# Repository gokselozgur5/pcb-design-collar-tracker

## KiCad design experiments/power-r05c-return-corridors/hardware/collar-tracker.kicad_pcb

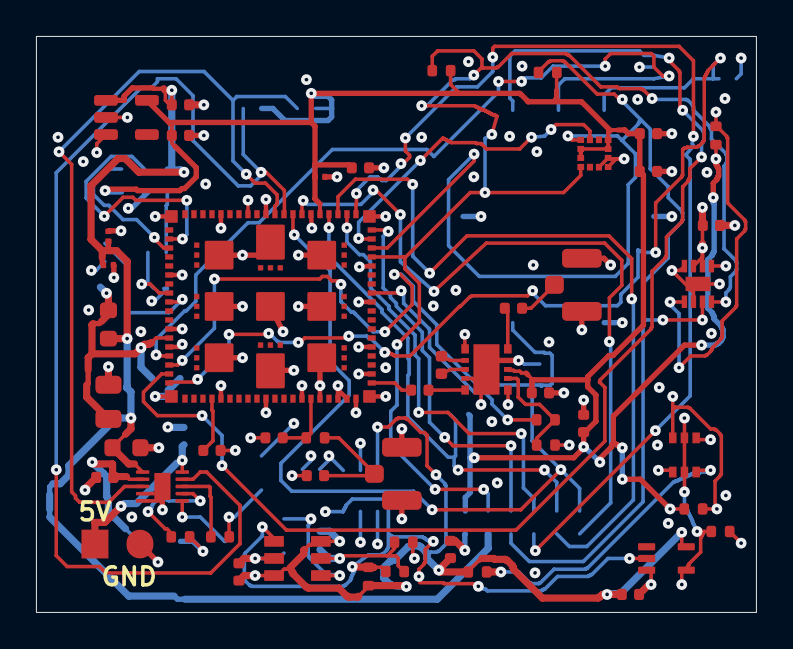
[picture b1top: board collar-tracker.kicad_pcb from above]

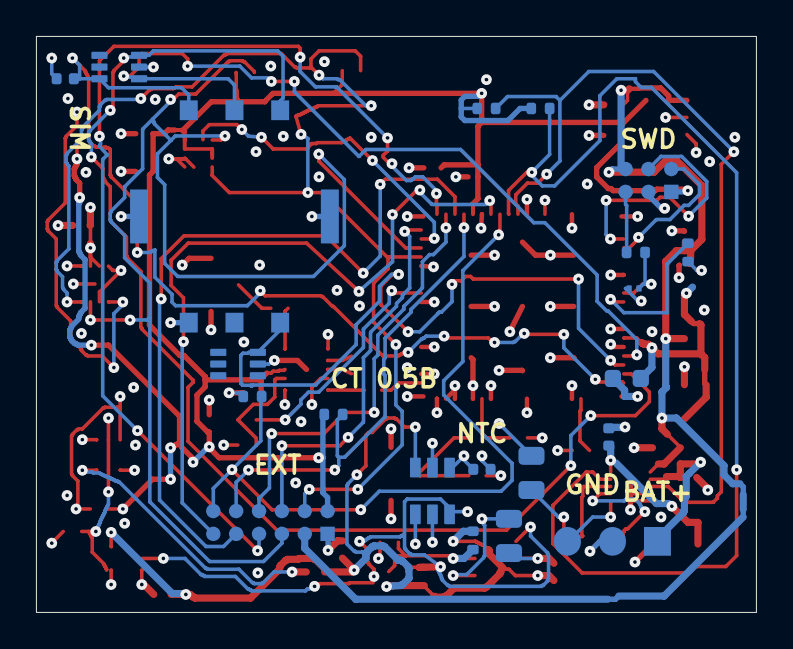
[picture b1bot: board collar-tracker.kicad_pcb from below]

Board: 4 copper layers, 40.0 x 32.0 mm, 71 parts (21 on the bottom side), 49 nets.

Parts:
C1: 1uF /10V; C1_C_0201_0603Metric
C2: 1uF /10V; C2_C_0201_0603Metric
C3: 47uF /10V; C3_C_0805_2012Metric
C4: 10uF /10V; C4_C_0603_1608Metric
C5: 100nF; C5_C_0201_0603Metric
C6: 4.7uF; C6_C_0402_1005Metric
C7: 4.7uF; C7_C_0402_1005Metric
C8: 100nF; C8_C_0201_0603Metric
C9: 1uF /16V X7R; C9_C_0805_2012Metric
C10: 100nF; C10_C_0402_1005Metric
C11: DNP / tune; C11_C_0402_1005Metric
C12: DNP / tune; C12_C_0402_1005Metric
C13: 39pF RF; C13_C_0402_1005Metric
C14: 39pF RF; C14_C_0402_1005Metric
C15: 100nF; C15_C_0402_1005Metric
C16: 1uF; C16_C_0402_1005Metric
C17: 1uF /10V; C17_C_0402_1005Metric
C18: 10uF /10V; C18_C_0603_1608Metric
C19: 1uF /10V; C19_C_0402_1005Metric
C20: 1uF; C20_C_0402_1005Metric
C21: 1uF; C21_C_0402_1005Metric
C23: 100nF; C23_C_0402_1005Metric
C24: 100nF; C24_C_0402_1005Metric
C25: 680nF /25V X7R; C25_C_0805_2012Metric
C26: 47nF /16V X7R; C26_C_0402_1005Metric
C27: 100nF /16V X7R; C27_C_0402_1005Metric
C28: 100nF /16V X7R; C28_C_0402_1005Metric
C29: 100nF /16V X7R; C29_C_0402_1005Metric
C30: 100nF /16V X7R; C30_C_0402_1005Metric
D1, D2: TPD4E1U06DCKR
FB1: 22R @100MHz; FB1_L_0603_1608Metric
J1: LTE antenna / 50R; J1_U.FL_Hirose_U.FL-R-SMT-1_Vertical
J2: GNSS antenna / passive; J2_U.FL_Hirose_U.FL-R-SMT-1_Vertical
J3: 5V charging input; J3_Solder_1x02_P2.5mm
J4: Protected cell + NTC; J4_Solder_1x03_P2.5mm
J5: DIGITAL health sensor interface; J5_Contact_2x06_P1.27mm
J6: SIM8051-6-0-14-00-A; SIM8051_6_0_14_00_A
J7: SWD / debug; J7_Contact_2x03_P1.27mm
L1: 9.1nH; L1_L_0402_1005Metric
Q1: DMN62D2UDW-7; Q1_SOT-363_SC-70-6
R1: 22k /1%; R1_R_0402_1005Metric
R2: 1k; R2_R_0402_1005Metric
R3: 0R / tune; R3_R_0402_1005Metric
R4: 1k; R4_R_0402_1005Metric
R5: 100k; R5_R_0402_1005Metric
R6: 18k /1%; R6_R_0402_1005Metric
R7: 3k /1%; R7_R_0402_1005Metric
R8: 10k; R8_R_0402_1005Metric
R9: 10k; R9_R_0402_1005Metric
R12: 4.7k; R12_R_0402_1005Metric
R13: 4.7k; R13_R_0402_1005Metric
R14: 100k; R14_R_0402_1005Metric
R15: 100k; R15_R_0402_1005Metric
R16: 10k /1%; R16_R_0402_1005Metric
R17: 1M /0.1%; R17_R_0402_1005Metric
R18: 130k /0.1%; R18_R_0402_1005Metric
R19: 16.9M /1%; R19_R_0402_1005Metric
R20: 10k /1%; R20_R_0402_1005Metric
R21: 22R /1%; R21_R_0402_1005Metric
R22: 1M /1%; R22_R_0402_1005Metric
R23: 100k /1%; R23_R_0402_1005Metric
U1: nRF9151-LACA; U1_LGA_9151_12.1x11.1mm
U2: SKY65943-11; U2_SKY65943_DK10171
U3: BQ25185DLHR; U3_Texas_DLH0010A_WSON-10-1EP_2.2x2mm_P0.4mm_EP0.9x1.5mm
U4: TPS7A0218PDBVR; U4_SOT-23-5
U5: LIS2DW12TR; U5_LGA-12_2x2mm_P0.5mm
U6: TPS3808G01DBVR; U6_SOT-23-6
U7: TPS3808G30DBVR; U7_SOT-23-6
U8: SN74LVC1G14DCKR; U8_SOT-353_SC-70-5
U9: MAX17048G+T10; U9_MAX17048_T822_3_90_0065E

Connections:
/ACC_INT: U1.58, U5.12
/AMP_IN: L1.2, U2.8
/BAT_NTC: J4.3, U3.6
/CHG_FAULT: R9.1, U1.70, U3.3
/CHG_STAT: R8.1, U1.69, U3.9
/COEX0: R4.1, U1.52
/DEBUG_RESET: J7.5, R2.2
/DEC0: C7.1, U1.24
/FG_ALERT: R23.2, U1.73, U9.5
/FILT_OUT: L1.1, U2.7
/GND: C1.2, C2.2, C3.2, C4.2, C5.2, C6.2, C7.2, C8.2, C9.2, C10.2, C11.2, C12.2, C15.2, C16.2, C17.2, C18.2, C19.2, C20.2, C21.2, C23.2, C24.2, C25.2, C26.2, C27.2, C28.2, C29.2, C30.2, D1.2, D2.2, J1.2, J2.2, J3.2, J4.2, J5.1, J6.5, J6.8, J7.3, Q1.1, Q1.4, R5.2, R6.2, R7.2, R15.2, R18.2, R22.2, U1.1, U1.7, U1.13, U1.15, U1.20, U1.25, U1.30, U1.34, U1.36, U1.38, U1.39, U1.40, U1.41, U1.43, U1.46, U1.51, U1.55, U1.60, U1.66, U1.71, U1.76, U1.105, U1.106, U1.107, U1.108, U1.109, U1.110, U1.111, U1.112, U1.113, U2.1, U2.4, U2.6, U2.9, U2.11, U3.4, U3.5, U3.11, U4.2, U5.6, U5.7, U5.8, U6.2, U7.2, U8.3, U9.1, U9.4, U9.6, U9.9
/GNSS_ANT: C14.1, J2.1
/GNSS_FEM_IN: C14.2, U2.5
/GNSS_FEM_OUT: C13.1, U2.10
/GNSS_LNA_EN: R4.2, R5.1, U2.2
/GPS_RF: C13.2, U1.42
/HEALTH_CS: J5.10, R14.1, U1.64
/HEALTH_EN: J5.12, R15.1, U1.68
/HEALTH_INT: J5.6, U1.59
/HEALTH_RESET: J5.11, U1.67
/I2C_SCL: J5.5, R13.1, U1.57, U5.1, U9.7
/I2C_SDA: J5.4, R12.1, U1.56, U5.4, U9.8
/ILIM_VSET: R6.1, U3.7
/ISET: R7.1, U3.8
/LTE_ANT: C12.1, J1.1, R3.2
/LTE_RF: C11.1, R3.1, U1.35
/NRF_ENABLE: C9.1, R1.2, U1.10, U7.5
/NRF_RESET: C8.1, R2.1, U1.9
/POWER_FAULT: Q1.2, Q1.5, R22.1, U8.4
/POWER_GOOD: R1.1, R16.2, R19.1, U6.1, U7.3, U8.2
/SIM_1V8: C10.1, D1.6, J6.1, U1.19
/SIM_CLK: D1.3, J6.3, U1.18
/SIM_IO: D2.3, J6.7, U1.17
/SIM_RST: D1.1, J6.2, U1.16
/SPI_MISO: J5.9, U1.63
/SPI_MOSI: J5.8, U1.62
/SPI_SCK: J5.7, U1.61
/SWDCLK: J7.4, U1.3
/SWDIO: J7.2, U1.4
/UV_DELAY: C25.1, U6.4
/UV_SENSE: R17.2, R18.1, R19.2, U6.5
/VBAT: C19.1, C30.1, J4.1, U3.2, U9.2, U9.3
/VDD_NRF: C3.1, C4.1, C27.1, C28.1, C29.1, FB1.2, R16.1, R17.1, R20.1, U1.14, U6.3, U6.6, U7.6, U8.5
/VIN_5V: C17.1, J3.1, U3.10
/VIO_1V8: C5.1, C6.1, C15.1, C16.1, C21.1, C23.1, C24.1, J5.2, J7.1, R8.2, R9.2, R12.2, R13.2, R14.2, R21.1, R23.1, U1.65, U2.3, U4.5, U5.2, U5.3, U5.9, U5.10
/VIO_DELAY: C26.1, U7.4
/VIO_DISCHARGE: Q1.6, R21.2
/VIO_ENABLE: Q1.3, R20.2, U4.3, U7.1
/VSYS: C1.1, C2.1, C18.1, C20.1, FB1.1, J5.3, J7.6, U3.1, U4.1

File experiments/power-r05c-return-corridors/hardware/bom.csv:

ref,value,mpn,footprint,dnp,onboard,status
U1,nRF9151-LACA,NRF9151-LACA-R,Collar033:U1_LGA_9151_12.1x11.1mm,False,True,candidate; LTE-M carrier unresolved
FB1,22R @100MHz,BLM18SD220SN1,Collar033:FB1_L_0603_1608Metric,False,True,Nordic recommended filter; verify rail impedance
C1,1uF /10V,GRM033R61A105ME15,Collar033:C1_C_0201_0603Metric,False,True,candidate
C2,1uF /10V,GRM033R61A105ME15,Collar033:C2_C_0201_0603Metric,False,True,candidate
C3,47uF /10V,GRM21BR61A476ME15,Collar033:C3_C_0805_2012Metric,False,True,candidate
C4,10uF /10V,GRM188R61A106MAAL,Collar033:C4_C_0603_1608Metric,False,True,candidate
C5,100nF,GRM033R60J104ME19,Collar033:C5_C_0201_0603Metric,False,True,candidate
C6,4.7uF,GRM155R60J475ME47,Collar033:C6_C_0402_1005Metric,False,True,candidate
C7,4.7uF,GRM155R60J475ME47,Collar033:C7_C_0402_1005Metric,False,True,candidate
C8,100nF,,Collar033:C8_C_0201_0603Metric,False,True,candidate
R1,22k /1%,,Collar033:R1_R_0402_1005Metric,False,True,Power sequencing resistor; exact AVL pending
C9,1uF /16V X7R,GRM21BR71C105KA01L,Collar05:C9_C_0805_2012Metric,False,True,Candidate; effective C 0.60 to 1.265 uF must be qualified
R2,1k,,Collar033:R2_R_0402_1005Metric,False,True,candidate
C10,100nF,,Collar033:C10_C_0402_1005Metric,False,True,SIM supply decoupling beside the upper contact row
R3,0R / tune,,Collar033:R3_R_0402_1005Metric,False,True,candidate
C11,DNP / tune,,Collar033:C11_C_0402_1005Metric,True,True,candidate
C12,DNP / tune,,Collar033:C12_C_0402_1005Metric,True,True,candidate
J1,LTE antenna / 50R,U.FL-R-SMT-1(10),Collar033:J1_U.FL_Hirose_U.FL-R-SMT-1_Vertical,False,True,bench connector; final FPC antenna TBD
U2,SKY65943-11,SKY65943-11,Collar033:U2_SKY65943_DK10171,False,True,DFM layout candidate; electrical validation pending
L1,9.1nH,LQW15AN9N1J00D,Collar033:L1_L_0402_1005Metric,False,True,candidate
C13,39pF RF,,Collar033:C13_C_0402_1005Metric,False,True,candidate
C14,39pF RF,,Collar033:C14_C_0402_1005Metric,False,True,candidate
J2,GNSS antenna / passive,U.FL-R-SMT-1(10),Collar033:J2_U.FL_Hirose_U.FL-R-SMT-1_Vertical,False,True,bench connector; final antenna/ESD TBD
R4,1k,,Collar033:R4_R_0402_1005Metric,False,True,candidate
R5,100k,,Collar033:R5_R_0402_1005Metric,False,True,candidate
C15,100nF,,Collar033:C15_C_0402_1005Metric,False,True,candidate
C16,1uF,,Collar033:C16_C_0402_1005Metric,False,True,candidate
J3,5V charging input,,Collar033:J3_Solder_1x02_P2.5mm,False,True,onboard contact pads; external device/fixture not selected
U3,BQ25185DLHR,BQ25185DLHR,Collar033:U3_Texas_DLH0010A_WSON-10-1EP_2.2x2mm_P0.4mm_EP0.9x1.5mm,False,True,DFM layout candidate; electrical validation pending
J4,Protected cell + NTC,,Collar033:J4_Solder_1x03_P2.5mm,False,True,onboard contact pads; external device/fixture not selected
C17,1uF /10V,,Collar033:C17_C_0402_1005Metric,False,True,candidate
C18,10uF /10V,,Collar033:C18_C_0603_1608Metric,False,True,candidate
C19,1uF /10V,,Collar033:C19_C_0402_1005Metric,False,True,candidate
R6,18k /1%,,Collar033:R6_R_0402_1005Metric,False,True,4.2V / 500mA input limit per BQ25185 table
R7,3k /1%,,Collar033:R7_R_0402_1005Metric,False,True,100mA provisional; battery approval required
R8,10k,,Collar033:R8_R_0402_1005Metric,False,True,candidate
R9,10k,,Collar033:R9_R_0402_1005Metric,False,True,candidate
U4,TPS7A0218PDBVR,TPS7A0218PDBVR,Collar033:U4_SOT-23-5,False,True,GPIO supply enabled by U7; Q1 forces enable low on a power fault
C20,1uF,,Collar033:C20_C_0402_1005Metric,False,True,candidate
C21,1uF,,Collar033:C21_C_0402_1005Metric,False,True,candidate
U5,LIS2DW12TR,LIS2DW12TR,Collar033:U5_LGA-12_2x2mm_P0.5mm,False,True,DFM layout candidate; electrical validation pending
C23,100nF,,Collar033:C23_C_0402_1005Metric,False,True,candidate
C24,100nF,,Collar033:C24_C_0402_1005Metric,False,True,candidate
R12,4.7k,,Collar033:R12_R_0402_1005Metric,False,True,candidate
R13,4.7k,,Collar033:R13_R_0402_1005Metric,False,True,candidate
J5,DIGITAL health sensor interface,,Collar033:J5_Contact_2x06_P1.27mm,False,True,onboard contact pads; external device/fixture not selected
R14,100k,,Collar033:R14_R_0402_1005Metric,False,True,candidate
R15,100k,,Collar033:R15_R_0402_1005Metric,False,True,candidate
J6,SIM8051-6-0-14-00-A,SIM8051-6-0-14-00-A,Collar04:SIM8051_6_0_14_00_A,False,True,SMT removable nano-SIM; 1.8V UICC and LTE-M/NB-IoT service required
J7,SWD / debug,,Collar033:J7_Contact_2x03_P1.27mm,False,True,onboard contact pads; external device/fixture not selected
D1,TPD4E1U06DCKR,TPD4E1U06DCKR,Collar04:TPD4E1U06DCKR,False,True,Three upper SIM contacts; short connector-side ESD routes
D2,TPD4E1U06DCKR,TPD4E1U06DCKR,Collar04:TPD4E1U06DCKR,False,True,Lower SIM data contact; direct connector-to-ESD-to-modem route
U6,TPS3808G01DBVR,TPS3808G01DBVR,Collar05:U6_SOT-23-6,False,True,Power schematic candidate; footprint drawing and physical validation pending
U7,TPS3808G30DBVR,TPS3808G30DBVR,Collar05:U7_SOT-23-6,False,True,Power schematic candidate; footprint drawing and physical validation pending
U8,SN74LVC1G14DCKR,SN74LVC1G14DCKR,Collar05:U8_SOT-353_SC-70-5,False,True,Power schematic candidate; footprint drawing and physical validation pending
Q1,DMN62D2UDW-7,DMN62D2UDW-7,Collar05:Q1_SOT-363_SC-70-6,False,True,Power schematic candidate; footprint drawing and physical validation pending
U9,MAX17048G+T10,MAX17048G+T10,Collar05:U9_MAX17048_T822_3_90_0065E,False,True,Power schematic candidate; footprint drawing and physical validation pending
R16,10k /1%,,Collar05:R16_R_0402_1005Metric,False,True,Candidate; specified tolerance and exact AVL required
R17,1M /0.1%,,Collar05:R17_R_0402_1005Metric,False,True,Candidate; specified tolerance and exact AVL required
R18,130k /0.1%,,Collar05:R18_R_0402_1005Metric,False,True,Candidate; specified tolerance and exact AVL required
R19,16.9M /1%,,Collar05:R19_R_0402_1005Metric,False,True,Candidate; specified tolerance and exact AVL required
R20,10k /1%,,Collar05:R20_R_0402_1005Metric,False,True,Candidate; specified tolerance and exact AVL required
R21,22R /1%,,Collar05:R21_R_0402_1005Metric,False,True,Candidate; specified tolerance and exact AVL required
R22,1M /1%,,Collar05:R22_R_0402_1005Metric,False,True,Candidate; specified tolerance and exact AVL required
R23,100k /1%,,Collar05:R23_R_0402_1005Metric,False,True,Candidate; specified tolerance and exact AVL required
C25,680nF /25V X7R,GRM219R71E684KA88D,Collar05:C25_C_0805_2012Metric,False,True,Candidate; effective capacitance and exact AVL require review
C26,47nF /16V X7R,,Collar05:C26_C_0402_1005Metric,False,True,Candidate; effective capacitance and exact AVL require review
C27,100nF /16V X7R,,Collar05:C27_C_0402_1005Metric,False,True,Candidate; effective capacitance and exact AVL require review
C28,100nF /16V X7R,,Collar05:C28_C_0402_1005Metric,False,True,Candidate; effective capacitance and exact AVL require review
C29,100nF /16V X7R,,Collar05:C29_C_0402_1005Metric,False,True,Candidate; effective capacitance and exact AVL require review
C30,100nF /16V X7R,,Collar05:C30_C_0402_1005Metric,False,True,Candidate; effective capacitance and exact AVL require review
